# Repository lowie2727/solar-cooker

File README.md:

# Solar cooker

This repository contains the [arduino code](arduino) and [pcb layout](kicad) for the testing station of our solar cooker.

# Contributing

This repository is no longer actively maintained. If you want to contribute to this project, you can always fork this repository.

# Final result

This is the test station built by the first generation of electronics students.

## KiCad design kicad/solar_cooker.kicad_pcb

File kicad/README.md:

# KiCad

## Installation

please install the latest kicad version from [kicad.org](https://www.kicad.org/download/)

## CADLAB (visual version control)
View this project on [CADLAB.io](https://cadlab.io/project/26616)

## v1

The v1 subfolder contains the current test phase of the project, which will end soon.

## v1.5

The v1.5 folder contains the documents for creating a custom board, in this version the Arduino Mega will still be needed.

## v2-beta

The folder v2-beta contains the documents for making a custom board, in this version the chip of the Arduino Mega is integrated on the board so no external Mega is needed anymore.

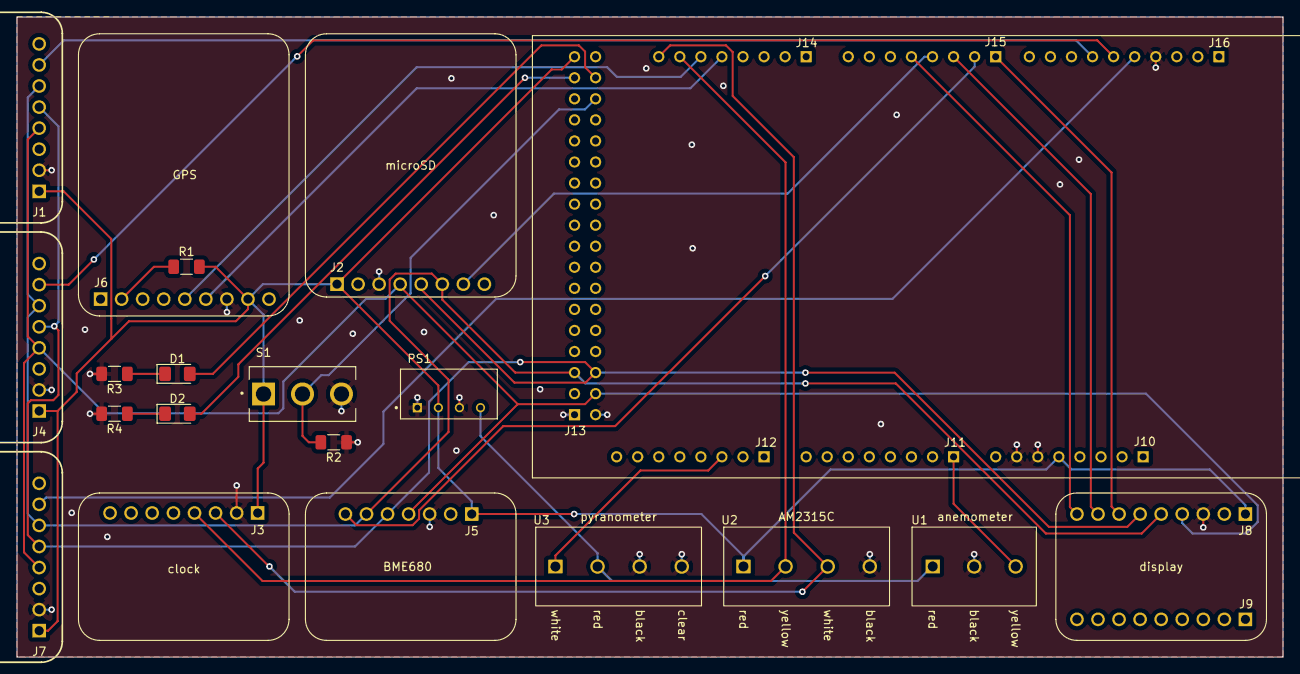
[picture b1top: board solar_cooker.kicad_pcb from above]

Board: 2 copper layers, 152.7 x 77.2 mm, 20 parts (1 on the bottom side), 26 nets.

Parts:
A1: A000067; ARDUINO_A000067
D1: LED_GREEN; LED_1206_3216Metric_Pad1.42x1.75mm_HandSolder
D2: LED_RED; LED_1206_3216Metric_Pad1.42x1.75mm_HandSolder
J1, J4, J7: Pt100
J2: microSD
J3: clock
J5: BME680
J6: GPS
J8: display
PS1: TBA_1-0519; CONV_TBA_1-0519
R1, R2: 10k; R_1206_3216Metric_Pad1.30x1.75mm_HandSolder
R3, R4: 150; R_1206_3216Metric_Pad1.30x1.75mm_HandSolder
S1: 500SSP1S2M2QEA; SW_500SSP1S2M2QEA
U1: anemometer; screw_terminal_3pin
U2: AM2315C; screw_terminal_4pin
U3: pyranometer; screw_terminal_4pin

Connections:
+5V: A1.5V_1 (+5V_1), A1.5V_3 (+5V_3), J1.1 (VIN), J2.1 (5V), J3.1 (VIN), J4.1 (VIN), J5.1 (VIN), J6.8 (VIN), J7.1 (VIN), J8.1 (Vin), PS1.2 (+VIN(VCC)), R1.2, S1.1, U2.1 (VCC)
+9V: PS1.4 (+VOUT), U1.1 (VCC), U3.2 (VCC)
/A0: A1.AD0, U1.3 (SIG)
/A10: A1.AD10, U3.1 (SIG)
/D3: A1.3, J8.9 (TCS)
/D4: A1.4, J2.7 (CS)
/D5: A1.5, J8.8 (RST)
/D6: A1.6, J5.7 (CS)
/D7: A1.7, J8.7 (DC)
/D11: A1.11, J1.7 (CS)
/D12: A1.12, J4.7 (CS)
/D13: A1.13, J7.7 (CS)
/D22: A1.22, D1.2 (A)
/D23: A1.23, D2.2 (A)
/D24: A1.24, R2.2, S1.2
/MISO: A1.50, J1.5 (SDO), J2.5 (DO), J4.5 (SDO), J5.5 (SDO), J7.5 (SDO), J8.6 (MISO)
/MOSI: A1.51, J1.6 (SDI), J2.6 (DI), J4.6 (SDI), J5.6 (SDI), J7.6 (SDI), J8.5 (MOSI)
/RX1: A1.19, J6.5 (TX)
/SCK: A1.52, J1.4 (CLK), J2.4 (CLK), J4.4 (CLK), J5.4 (SCK), J7.4 (CLK), J8.4 (SCK)
/SCL: A1.21, J3.3 (SCL), U2.3 (SCL)
/SDA: A1.20, J3.4 (SDA), U2.2 (SDA)
/TX1: A1.18, J6.6 (RX)
GND: A1.GND1, A1.GND2, A1.GND3, A1.GND4, A1.GND5, J1.2 (GND), J2.3 (GND), J3.2 (GND), J4.2 (GND), J5.3 (GND), J6.7 (GND), J7.2 (GND), J8.3 (GND), PS1.1 (-VIN(GND)), PS1.3 (-VOUT), R2.1, R3.2, R4.2, S1.3, U1.2 (GND), U2.4 (GND), U3.3 (GND), U3.4 (GND)
unnamed: D1.1 (K), R3.1
unnamed: D2.1 (K), R4.1
unnamed: J6.2 (EN), R1.1

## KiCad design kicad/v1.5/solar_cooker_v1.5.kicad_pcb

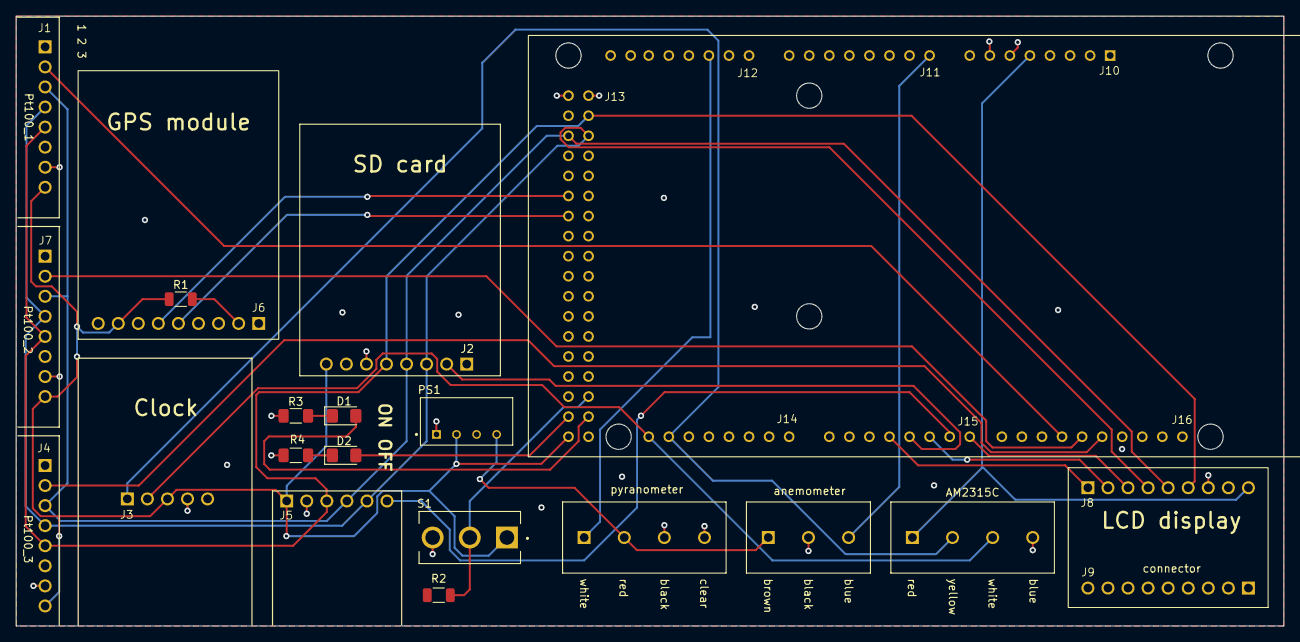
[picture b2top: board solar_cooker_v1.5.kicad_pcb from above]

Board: 2 copper layers, 160.5 x 77.2 mm, 20 parts (0 on the bottom side), 26 nets.

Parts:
A1: A000067; ARDUINO_A000067
D1, D2: LED; LED_1206_3216Metric_Pad1.42x1.75mm_HandSolder
J1, J4, J7: Pt100
J2: microSD
J3: clock_module; clockModule
J5: BME680
J6: GPS
J8: display
PS1: TBA_1-0519; CONV_TBA_1-0519
R1, R2: R_Small; R_1206_3216Metric
R3, R4: R_Small; R_1206_3216Metric_Pad1.30x1.75mm_HandSolder
S1: 500SSP1S2M2QEA; SW_500SSP1S2M2QEA
U1: anemometer; screw_terminal_3pin
U2: AM2315C; screw_terminal_4pin
U3: pyranometer; screw_terminal_4pin

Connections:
+5V: A1.5V_1 (+5V_1), A1.5V_3 (+5V_3), J1.8 (VIN), J2.8 (5V), J3.3 (VCC), J4.8 (VIN), J5.1 (VCC), J6.8 (VIN), J7.8 (VIN), J8.9 (Vin), PS1.2 (+VIN(VCC)), R1.2, S1.1, U2.1 (VCC)
+9V: PS1.4 (+VOUT), U1.1 (VCC), U3.2 (VCC)
/A0: A1.AD0, U1.3 (SIG)
/A10: A1.AD10, U3.1 (SIG)
/D3: A1.3, J8.1 (TCS)
/D4: A1.4, J2.2 (CS)
/D5: A1.5, J8.2 (RST)
/D6: A1.6, J5.6 (CS)
/D7: A1.7, J8.3 (DC)
/D11: A1.11, J1.2 (CS)
/D12: A1.12, J7.2 (CS)
/D13: A1.13, J4.2 (CS)
/D22: A1.22, D1.2 (A)
/D23: A1.23, D2.2 (A)
/D24: A1.24, R2.2, S1.2
/D43: A1.43, J6.5 (TX)
/D45: A1.45, J6.6 (RX)
/MISO: A1.50, J1.4 (SDO), J2.3 (DI), J4.4 (SDO), J5.5 (SDO), J7.4 (SDO), J8.4 (MISO)
/MOSI: A1.51, J1.3 (SDI), J2.4 (DO), J4.3 (SDI), J5.4 (SDA), J7.3 (SDI), J8.5 (MOSI)
/SCK: A1.52, J1.5 (CLK), J2.5 (CLK), J4.5 (CLK), J5.3 (SCL), J7.5 (CLK), J8.6 (SCK)
/SCL: A1.21, J3.2 (SCL), U2.3 (SCL)
/SDA: A1.20, J3.1 (SDA), U2.2 (SDA)
GND: A1.GND1, A1.GND2, A1.GND3, A1.GND4, A1.GND5, J1.7 (GND), J2.6 (GND), J3.4 (GND), J4.7 (GND), J5.2 (GND), J6.7 (GND), J7.7 (GND), J8.7 (GND), PS1.1 (-VIN(GND)), R2.1, R3.2, R4.2, S1.3, U1.2 (GND), U2.4 (GND), U3.3 (GND), U3.4 (GND)
unnamed: D1.1 (K), R3.1
unnamed: D2.1 (K), R4.1
unnamed: J6.2 (EN), R1.1

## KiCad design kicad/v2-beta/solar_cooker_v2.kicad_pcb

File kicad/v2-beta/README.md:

# v2

## Sources

- [Arduino from scratch](https://rheingoldheavy.com/arduino-from-scratch-part-8-atmega16u2-subsystem/)
- [official Arduino Uno Rev3 schematic](https://content.arduino.cc/assets/UNO-TH_Rev3e_sch.pdf)

## Useful links

If you cannot find a component in the standard KiCad library, you can visit the following sites.

- [snapeda.com](https://www.snapeda.com/)
- [findchips.com](https://www.findchips.com/)
- [componentsearchengine.com](https://componentsearchengine.com/)
- [ultralibrarian.com](https://www.ultralibrarian.com/)

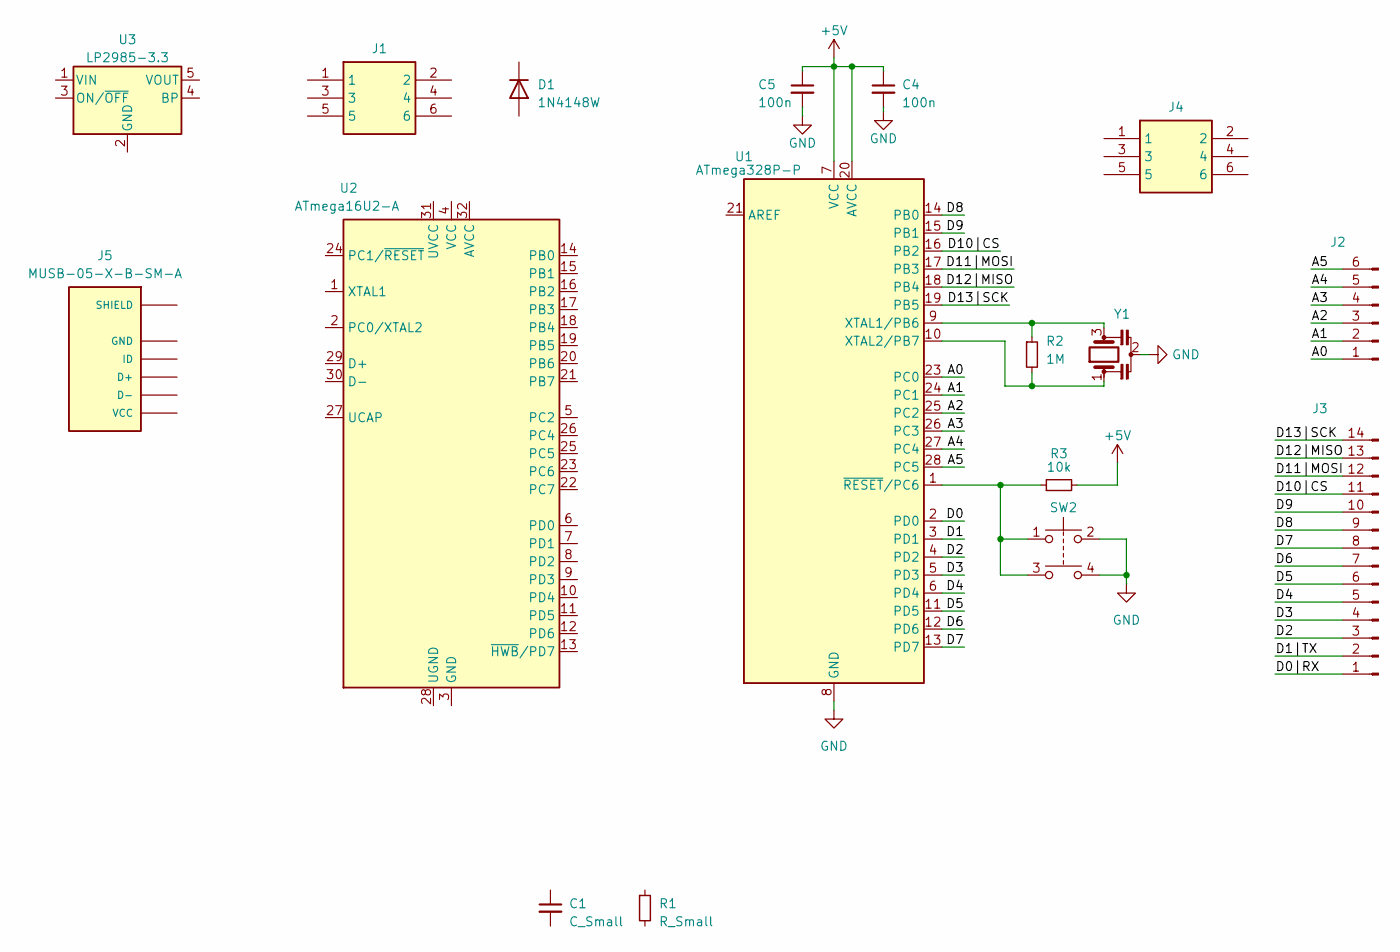
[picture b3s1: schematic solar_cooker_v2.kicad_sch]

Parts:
C1: C_Small; C_01005_0402Metric
C4, C5: 100n; C_01005_0402Metric
D1: 1N4148W; D_SOD-123
J1, J4: M20-9980346; HDRV6W64P254_2X3_762X508X868P
J2: Conn_01x06_Pin; PinSocket_1x06_P2.54mm_Vertical
J3: Conn_01x14_Pin; PinSocket_1x14_P2.54mm_Vertical
J5: MUSB-05-X-B-SM-A; SAMTEC_MUSB-05-X-B-SM-A
R1: R_Small; R_01005_0402Metric
R2: 1M; R_01005_0402Metric
R3: 10k; R_01005_0402Metric
SW2: SW_Push_Dual; SMT3-01-Z
U1: ATmega328P-P; DIP-28_W7.62mm
U2: ATmega16U2-A; TQFP-32_7x7mm_P0.8mm
U3: LP2985-3.3; SOT-23-5
Y1: Resonator; OSC_CSTCE16M0V53-R0

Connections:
+5V: C4.1, C5.1, R3.2, U1.7 (VCC), U1.20 (AVCC)
/A0: J2.1, U1.23 (PC0)
/A1: J2.2, U1.24 (PC1)
/A2: J2.3, U1.25 (PC2)
/A3: J2.4, U1.26 (PC3)
/A4: J2.5, U1.27 (PC4)
/A5: J2.6, U1.28 (PC5)
/D0: U1.2 (PD0)
/D0|RX: J3.1
/D1: U1.3 (PD1)
/D1|TX: J3.2
/D2: J3.3, U1.4 (PD2)
/D3: J3.4, U1.5 (PD3)
/D4: J3.5, U1.6 (PD4)
/D5: J3.6, U1.11 (PD5)
/D6: J3.7, U1.12 (PD6)
/D7: J3.8, U1.13 (PD7)
/D8: J3.9, U1.14 (PB0)
/D9: J3.10, U1.15 (PB1)
/D10|CS: J3.11, U1.16 (PB2)
/D11|MOSI: J3.12, U1.17 (PB3)
/D12|MISO: J3.13, U1.18 (PB4)
/D13|SCK: J3.14, U1.19 (PB5)
GND: C4.2, C5.2, SW2.2, SW2.4, U1.8 (GND), U1.22 (GND), Y1.2
unnamed: J5.S1 (SHIELD), J5.S2 (SHIELD), J5.S3 (SHIELD), J5.S4 (SHIELD)
unnamed: R2.1, U1.9 (XTAL1/PB6), Y1.3
unnamed: R2.2, U1.10 (XTAL2/PB7), Y1.1
unnamed: R3.1, SW2.1, SW2.3, U1.1 (~RESET/PC6)

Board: 2 copper layers, 18 parts (0 on the bottom side), 24 nets, no tracks yet.

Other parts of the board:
D2: LED-1206

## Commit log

2023-03-07 blink
2023-03-14 added outside temperature sensor and microSD card
2023-03-14 added KiCad project
2023-03-14 CADLAB integration
2023-03-15 update microSD
2023-03-15 added custom microSD component
2023-03-15 added clockModule
2023-03-16 kicad project update
2023-03-19 added e-Paper + minor improvements
2023-03-20 e-Paper printing variable that changes
2023-03-20 files are generated based on the current time
2023-03-21 arduino workflow
2023-03-21 added GPS
2023-03-22 Arduino CLI implementation
2023-03-22 arduino workflow update
2023-03-27 update arduino main README.md + formatting
2023-03-30 added switch
2023-03-30 added anemometer
2023-03-30 anemometer + switch schematic
2023-03-30 added BME680
2023-03-31 schematic and documentation update
2023-03-31 folder structure improvement
2023-04-04 added PT100
2023-04-04 update main
2023-04-07 update main
    added switch with red and green leds, starting measurements with the switch creates new file
2023-04-08 contributions Ruben
2023-04-08 removed temp folder
2023-04-10 added pyranometer
2023-04-10 added GPS schematic
2023-04-10 GPS schematic update
2023-04-10 added KiCad v2
    work in progress
2023-04-10 KiCad v2 update
2023-04-11 update main + added schematic AM2315
2023-04-11 update main + cleanup
2023-04-13 added e-Paper and pyrano to main
2023-04-14 improved e-Paper layout
2023-04-14 clockModule update in main
2023-04-14 compressed code
2023-04-14 compressed code and hPa instead of Pa
2023-04-15 added logo UHasselt and UNILU
2023-04-23 platformIO migration
2023-05-01 memory optimisation + minor improvements
2023-05-01 kicad update
2023-05-02 removed e-Paper and GPS + minor improvements
2023-05-02 platformIO workflow
2023-05-02 added KiCad v1.5 + workflow improvement
2023-05-03 update csv headers + file name fix
2023-05-03 back to using String
2023-05-04 documentation update
2023-05-05 added Arduino Mega KiCad
2023-05-05 pcb has now 3 pt100 sensors
2023-05-07 added GPS to pcb
2023-05-07 routing update
2023-05-07 added DC-DC converter
2023-05-07 converter scheme and footprint added
2023-05-08 drc fix
2023-05-08 added display
2023-05-08 added display connections
2023-05-08 routed display
2023-05-08 added gps connections
2023-05-09 updated display connections
2023-05-09 conflict removed
2023-05-09 rerouted display and gps
2023-05-14 updatet pcb
2023-05-14 pcb minor fix
2023-05-16 silkscreen fix for order v1
2023-05-28 gps fix
2023-05-29 kicad structure improvement
2023-06-05 fixed GPS and clock module in kicad
2023-06-06 footprints update
2023-06-08 all footprints ready
2023-06-08 PCB routing and footprints done
2023-06-08 silkscreen update
2023-06-08 structure improvement kicad + added connectors
2023-06-09 bom generation from schematic
2023-06-09 arduino mega footprint update + 3D view added
2023-06-09 minor silkscreen fix
2023-06-09 minor update silkscreen
2023-06-09 order v2
2023-06-09 BOM generation update
    now uses KiBoM
2023-06-10 project files rename + connector improvement
2023-06-10 Electrical Rules Checker fix
    there are still some issues that need to be resolved
2023-06-20 added lcd code
2023-06-20 LCD fix
2023-06-20 clock code update + code cleanup
2023-06-20 kicad 9V DCDC convertor Vout- fix + rename clock
2023-06-20 microSD module fix kicad
    MISO and MOSI flipped
2023-06-20 GPS code update
2023-06-23 new anemometer code fix
2023-06-23 update main to show data on display
2023-06-23 GPS code change + minor fixes
2023-06-27 arduino display update in main (still broken)
    writing to file not possible when using display
    AM2315C still buggy (faulty sensor)
    not all sensor data visible on screen yet
2023-06-28 sdFat debug program
2023-07-10 AM2315C update
2023-07-10 components visible on display
2023-07-10 added units
2023-07-12 separate program for SD and LCD
2023-07-12 updated 3D model kicad
2023-07-15 serial monitor debug update
2023-07-18 microSD and screen working in test.cpp
2023-07-19 added avg temp and slope
2023-07-19 fixed previous mistake
2023-07-19 fixed some display mistakes and finished slow function
2023-07-19 test.cpp 3 Pt100 sensors update
2023-07-22 fixed slope function
2023-07-22 KiCad 3D view update
2023-07-22 Arduino README.md update
2023-07-22 main README.md update
2023-07-22 KiCad README.md update
2023-07-24 silkscreen update + schematic improvements
2023-07-25 components README.md update
2023-08-07 added slope in main on screen
2023-11-08 archiving repository
